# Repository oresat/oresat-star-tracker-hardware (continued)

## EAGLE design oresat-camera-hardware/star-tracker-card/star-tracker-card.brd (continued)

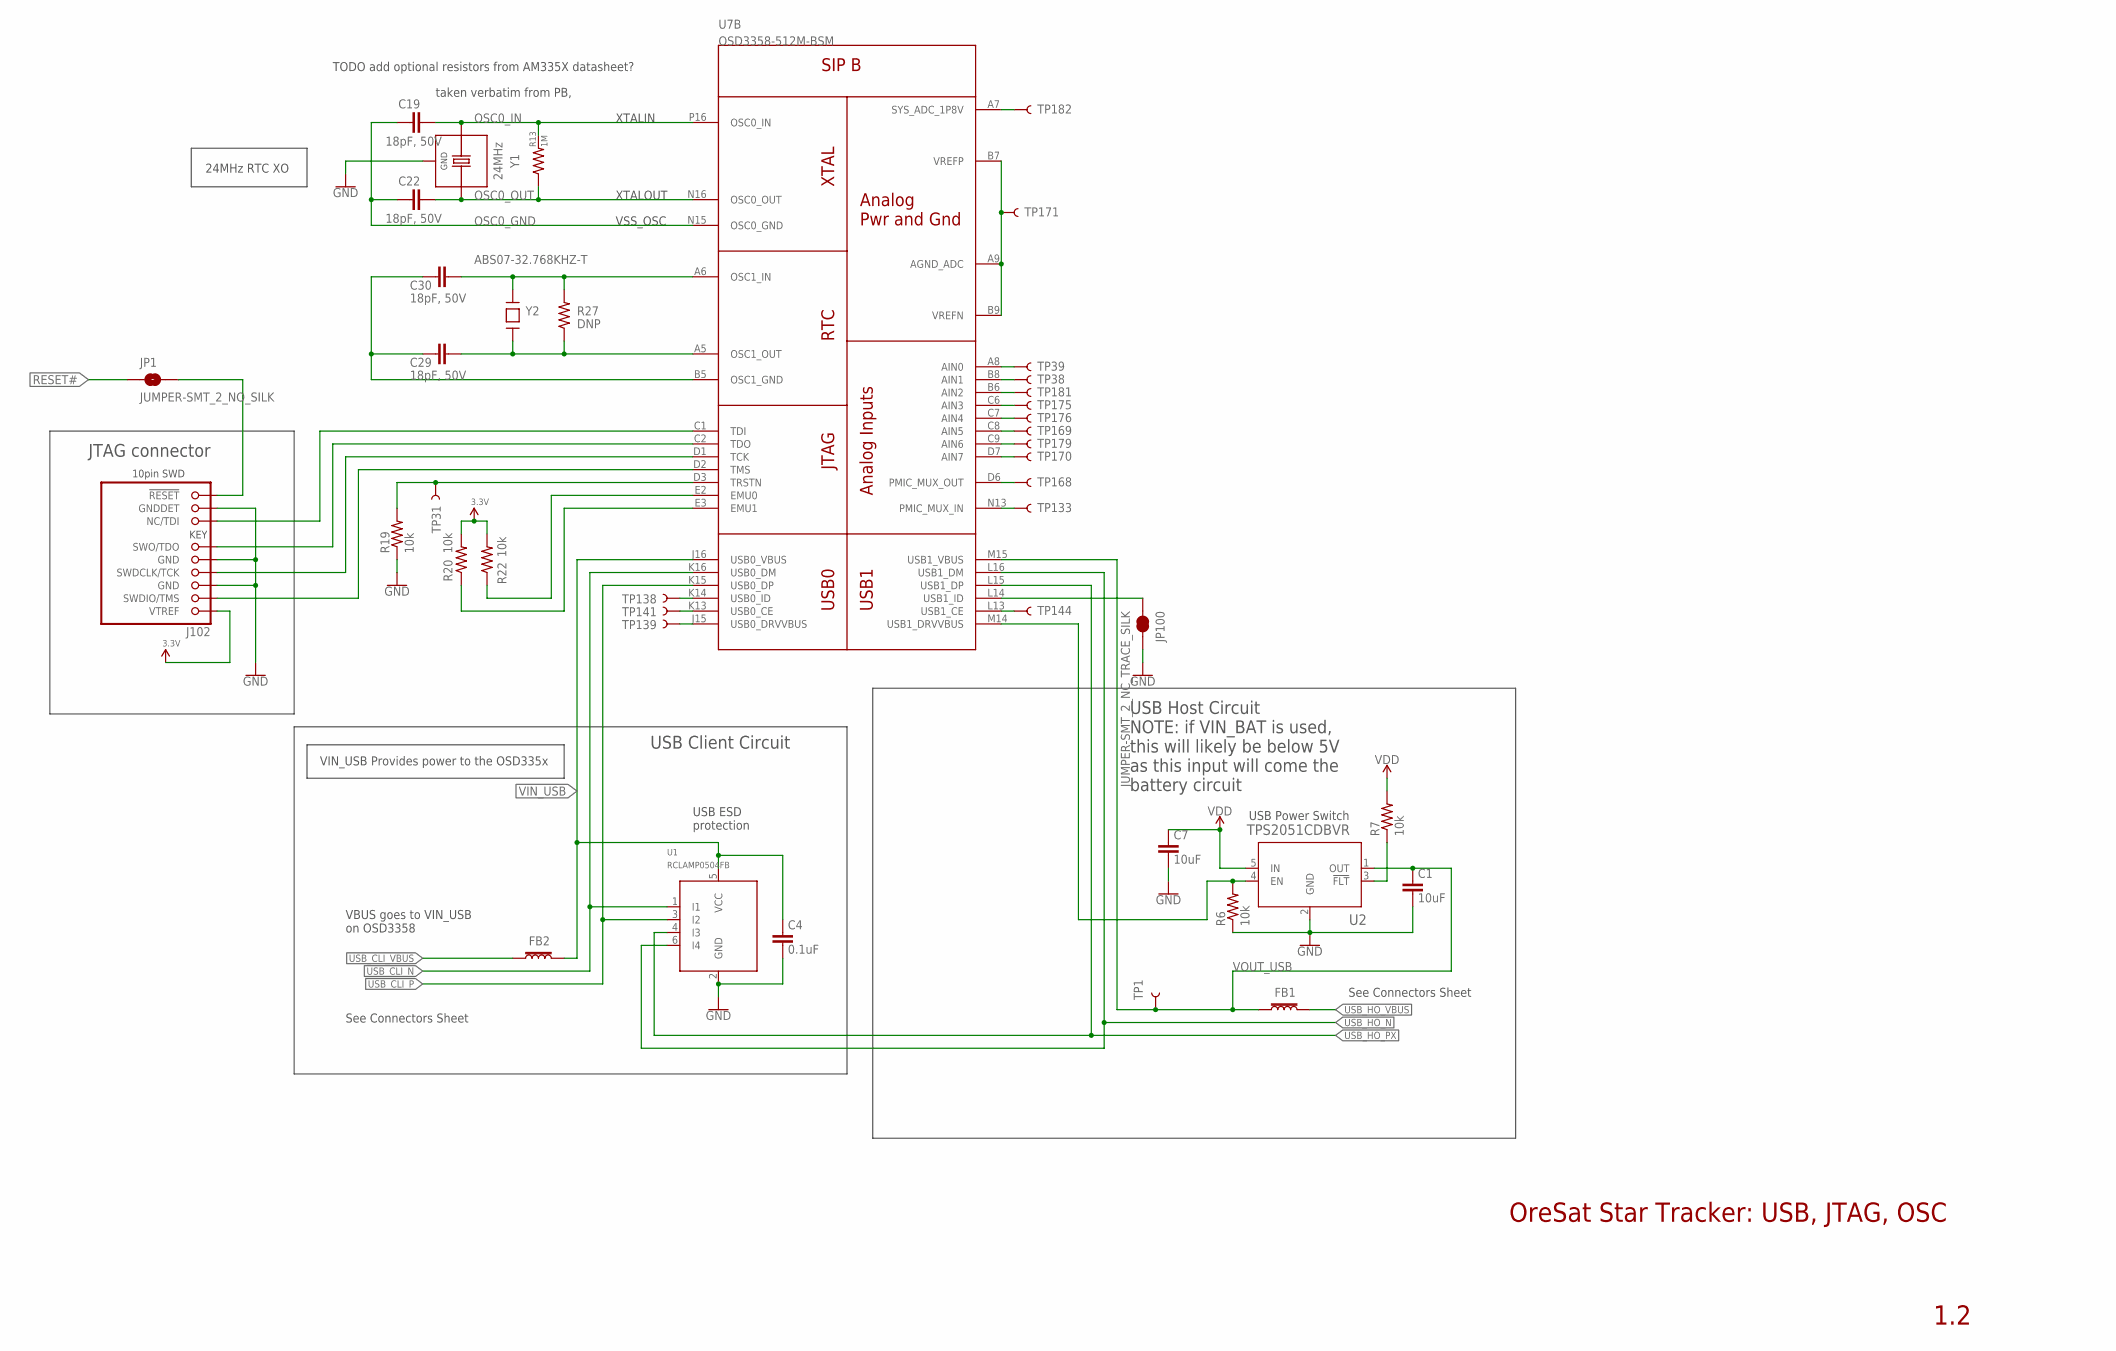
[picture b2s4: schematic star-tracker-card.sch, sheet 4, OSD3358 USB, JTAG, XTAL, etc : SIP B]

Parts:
C1, C7: 10uF; .0805-B
C4: 0.1uF; .0603-A
C19, C22, C29, C30: 18pF, 50V; .0603-A
FB1, FB2: 30Ω/1.8A; 0603; MPN BLM18KG300JH1D
J102: FTSH-105-XX-X-DV-K; CON10_2X5_DUK_FTSH
JP1: JUMPER-SMT_2_NO_SILK; SMT-JUMPER_2_NO_SILK
JP100: JUMPER-SMT_2_NC_TRACE_SILK; SMT-JUMPER_2_NC_TRACE_SILK
R6, R7, R19, R20, R22: 10k; .0603-A
R13: 1M; .0603-A
R27: DNP; .0603-A
TP1, TP31, TP38, TP39, TP133, TP138, TP139, TP141, TP144, TP168, TP169, TP170, TP171, TP175, TP176, TP179, TP181, TP182: TEST-POINT3X4; PAD.03X.04
U1: RCLAMP0504FB; SC70-6
U2: TPS2051CDBVR; DBV5
U7: OSD3358-512M-BSM; OSD335X-BGA-256
Y1: 24MHz; 5X3.2-4SMD
Y2: ABS07-32.768KHZ-T; CRYSTAL_3.2X1.5

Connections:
3.3V: J102.1 (VTREF), R20.2, R22.2; also elsewhere on the board
GND: C1.2, C4.2, C7.2, J102.3 (GND), J102.5 (GND), J102.9 (GNDDET), JP100.2, R6.1, R19.1, U1.2 (GND), U2.2 (GND), Y1.2 (GND), Y1.4 (GND); also elsewhere on the board
unnamed: TP171.P$1, U7.A9 (AGND_ADC), U7.B7 (VREFP), U7.B9 (VREFN)
unnamed: TP170.P$1, U7.D7 (AIN7)
unnamed: TP179.P$1, U7.C9 (AIN6)
unnamed: TP169.P$1, U7.C8 (AIN5)
unnamed: TP176.P$1, U7.C7 (AIN4)
unnamed: TP175.P$1, U7.C6 (AIN3)
unnamed: TP181.P$1, U7.B6 (AIN2)
unnamed: TP38.P$1, U7.B8 (AIN1)
unnamed: TP39.P$1, U7.A8 (AIN0)
unnamed: TP141.P$1, U7.K13 (USB0_CE)
unnamed: TP139.P$1, U7.J15 (USB0_DRVVBUS)
unnamed: TP182.P$1, U7.A7 (SYS_ADC_1P8V)
unnamed: TP168.P$1, U7.D6 (PMIC_MUX_OUT)
unnamed: R20.1, U7.E3 (EMU1)
unnamed: TP144.P$1, U7.L13 (USB1_CE)
unnamed: R22.1, U7.E2 (EMU0)
unnamed: JP100.1, U7.L14 (USB1_ID)
unnamed: TP138.P$1, U7.K14 (USB0_ID)
unnamed: J102.10 (!RESET), JP1.2
unnamed: J102.6 (SWO/TDO), U7.C2 (TDO)
unnamed: J102.4 (SWDCLK/TCK), U7.D1 (TCK)
unnamed: J102.2 (SWDIO/TMS), U7.D2 (TMS)
unnamed: R6.2, U2.4 (EN), U7.M14 (USB1_DRVVBUS)
unnamed: R7.1, U2.3 (!FLT)
unnamed: J102.8 (NC/TDI), U7.C1 (TDI)
unnamed: R19.2, TP31.P$1, U7.D3 (TRSTN)
OSC0_GND: C19.1, C22.1, U7.N15 (OSC0_GND)
OSC0_IN: C19.2, R13.2, U7.P16 (OSC0_IN), Y1.1 (X1)
OSC0_OUT: C22.2, R13.1, U7.N16 (OSC0_OUT), Y1.3 (X2)
OSC1_GND1: C29.2, C30.2, U7.B5 (OSC1_GND)
OSC1_IN1: C30.1, R27.2, U7.A6 (OSC1_IN), Y2.P$2
OSC1_OUT1: C29.1, R27.1, U7.A5 (OSC1_OUT), Y2.P$1
PMIC_MUX_IN: TP133.P$1, U7.N13 (PMIC_MUX_IN)
RESET#: JP1.1; also elsewhere on the board
USB_CLI_N: U1.1 (I1), U7.K16 (USB0_DM); also elsewhere on the board
USB_CLI_P: U1.3 (I2), U7.K15 (USB0_DP); also elsewhere on the board
USB_CLI_VBUS: FB2.1; also elsewhere on the board
USB_HO_N: U1.6 (I4), U7.L16 (USB1_DM); also elsewhere on the board
USB_HO_PX: U1.4 (I3), U7.L15 (USB1_DP); also elsewhere on the board
USB_HO_VBUS: FB1.2; also elsewhere on the board
VDD: C7.1, R7.2, U2.5 (IN); also elsewhere on the board
VIN_USB: C4.1, FB2.2, U1.5 (VCC), U7.J16 (USB0_VBUS); also elsewhere on the board
VOUT_USB: C1.1, FB1.1, TP1.P$1, U2.1 (OUT), U7.M15 (USB1_VBUS)

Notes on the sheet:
taken verbatim from PB,
VBUS goes to VIN_USB on OSD3358
USB ESD protection
USB Host Circuit NOTE: if VIN_BAT is used, this will likely be below 5V as this input will come the battery circuit
USB Power Switch
JTAG connector
USB Client Circuit
24MHz RTC XO
See Connectors Sheet
TODO add optional resistors from AM335X datasheet?
XTALIN
XTALOUT
VSS_OSC
VIN_USB Provides power to the OSD335x
OreSat Star Tracker: USB, JTAG, OSC
1.2

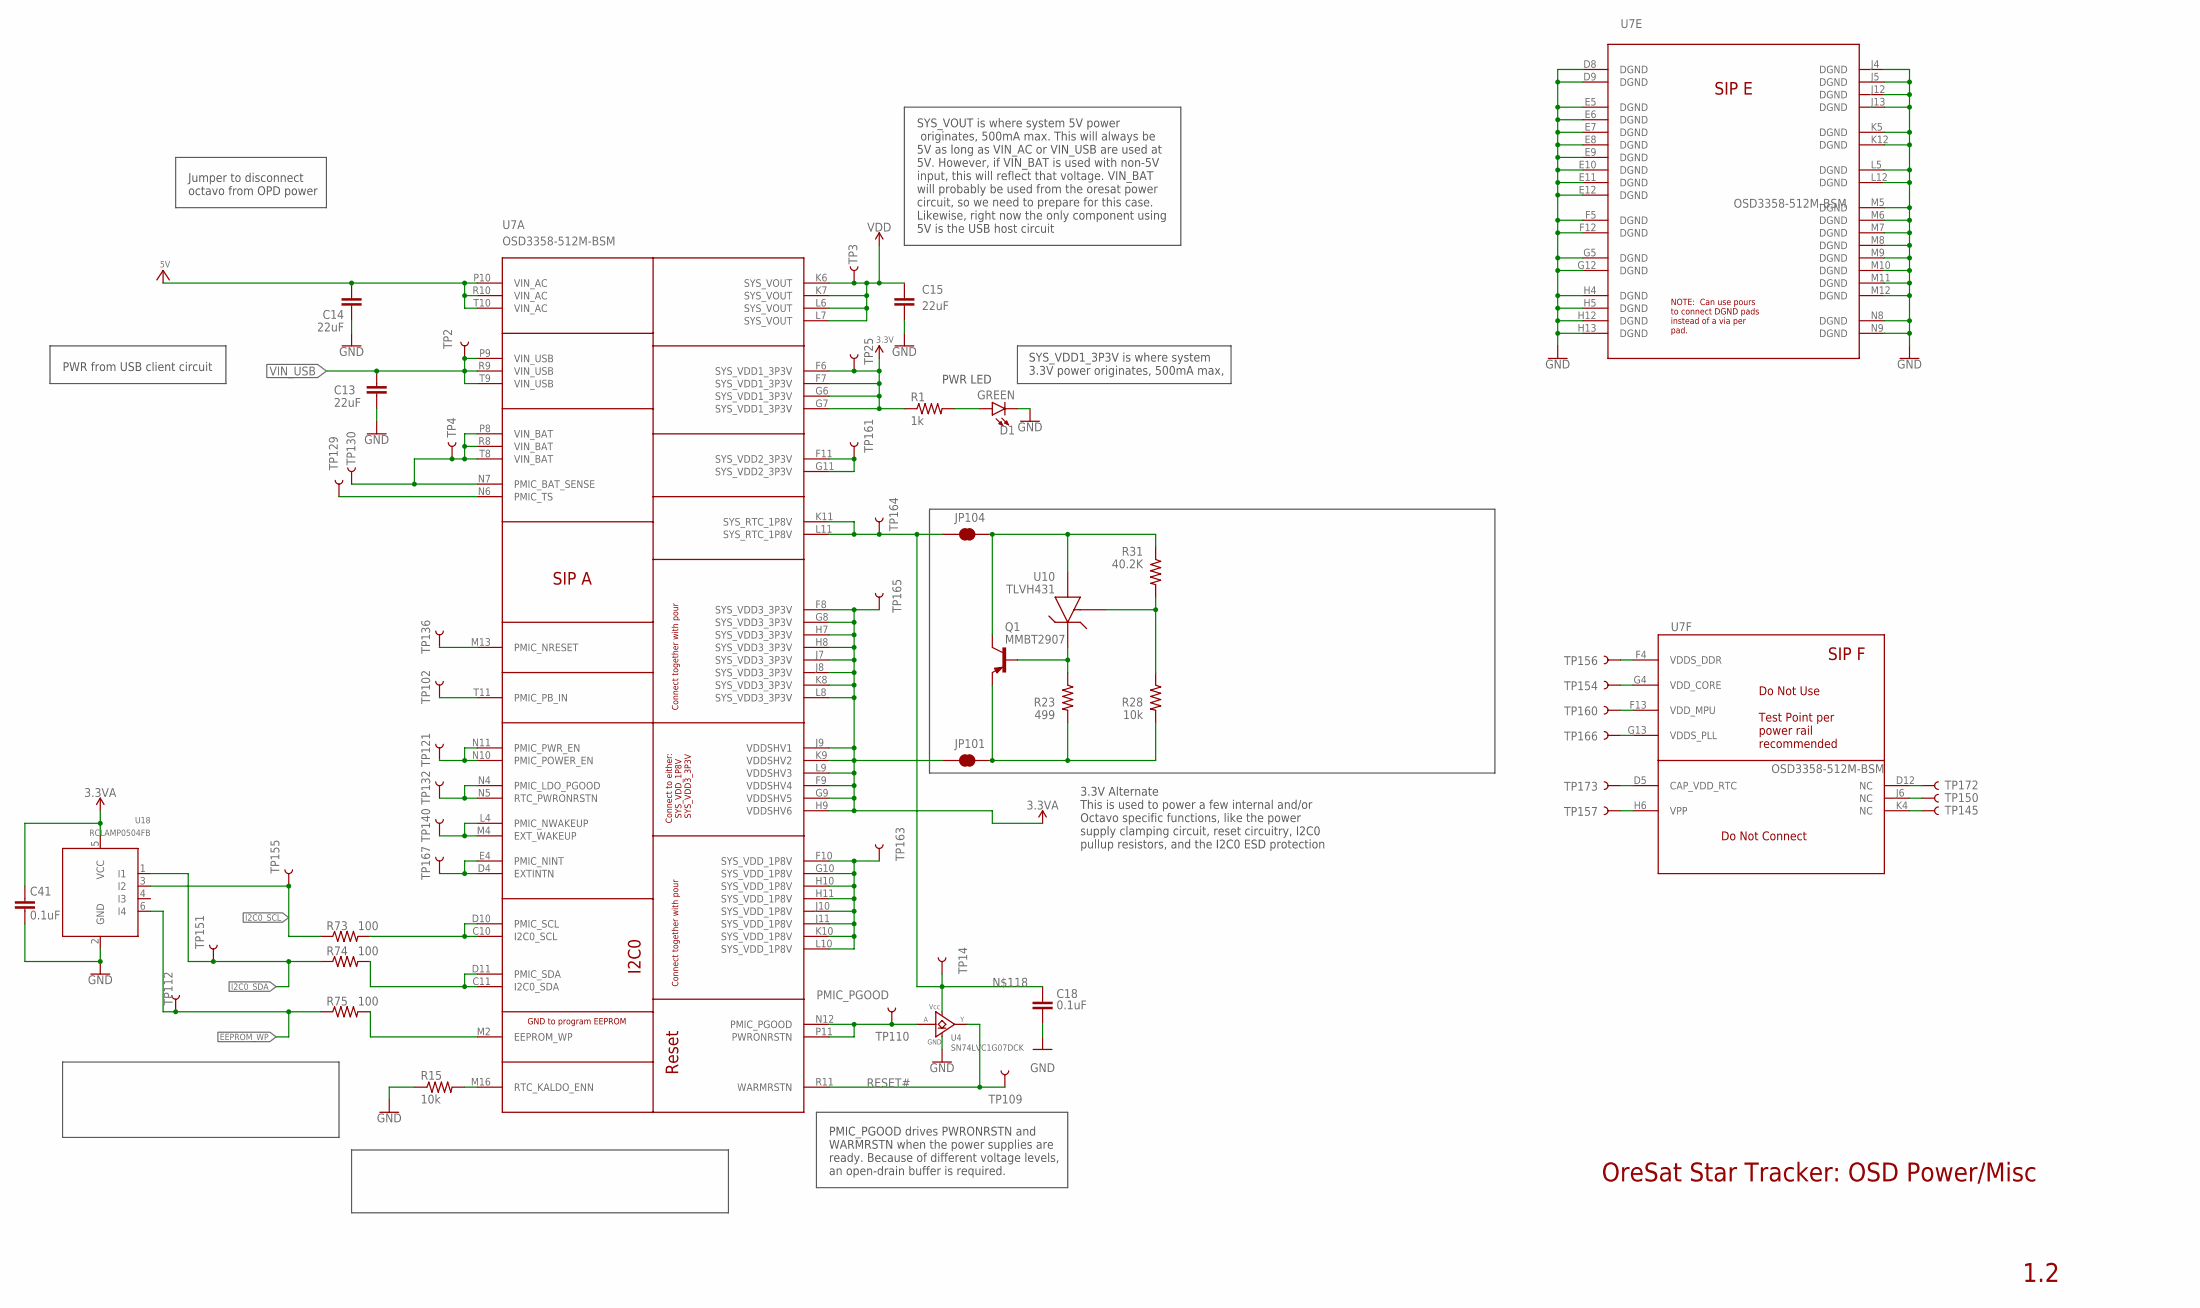
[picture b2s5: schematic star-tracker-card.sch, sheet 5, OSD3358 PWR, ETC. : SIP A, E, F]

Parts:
C13, C14, C15: 22uF; C1210
C18, C41: 0.1uF; .0603-A
D1: GREEN; LED-0603
JP101, JP104: JUMPER-SMT_2_NC_TRACE_SILK; SMT-JUMPER_2_NC_TRACE_SILK
Q1: MMBT2907; SOT23-BEC
R1: 1k; .0603-A
R15, R28: 10k; .0603-A
R23: 499; .0603-A
R31: 40.2K; .0603-A
R73, R74, R75: 100; .0603-A
TP2, TP3, TP4, TP14, TP25, TP102, TP109, TP110, TP112, TP121, TP129, TP130, TP132, TP136, TP140, TP145, TP150, TP151, TP154, TP155, TP156, TP157, TP160, TP161, TP163, TP164, TP165, TP166, TP167, TP172, TP173: TEST-POINT3X4; PAD.03X.04
U4: SN74LVC1G07DCK; C70(TI-DCK)
U7: OSD3358-512M-BSM; OSD335X-BGA-256
U10: TLVH431; SOT23-3
U18: RCLAMP0504FB; SC70-6

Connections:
3.3V: R1.1, TP25.P$1, U7.F6 (SYS_VDD1_3P3V), U7.F7 (SYS_VDD1_3P3V), U7.G6 (SYS_VDD1_3P3V), U7.G7 (SYS_VDD1_3P3V); also elsewhere on the board
3.3VA: C41.1, JP101.1, TP165.P$1, U7.F8 (SYS_VDD3_3P3V), U7.F9 (VDDSHV4), U7.G8 (SYS_VDD3_3P3V), U7.G9 (VDDSHV5), U7.H7 (SYS_VDD3_3P3V), U7.H8 (SYS_VDD3_3P3V), U7.H9 (VDDSHV6), U7.J7 (SYS_VDD3_3P3V), U7.J8 (SYS_VDD3_3P3V), U7.J9 (VDDSHV1), U7.K8 (SYS_VDD3_3P3V), U7.K9 (VDDSHV2), U7.L8 (SYS_VDD3_3P3V), U7.L9 (VDDSHV3), U18.5 (VCC)
5V: C14.1, U7.P10 (VIN_AC), U7.R10 (VIN_AC), U7.T10 (VIN_AC); also elsewhere on the board
EEPROM_WP: R75.1, TP112.P$1, U18.6 (I4); also elsewhere on the board
GND: C13.2, C14.2, C15.2, C18.2, C41.2, D1.C, R15.1, U4.3 (GND), U7.D8 (DGND), U7.D9 (DGND), U7.E5 (DGND), U7.E6 (DGND), U7.E7 (DGND), U7.E8 (DGND), U7.E9 (DGND), U7.E10 (DGND), U7.E11 (DGND), U7.E12 (DGND), U7.F5 (DGND), U7.F12 (DGND), U7.G5 (DGND), U7.G12 (DGND), U7.H4 (DGND), U7.H5 (DGND), U7.H12 (DGND), U7.H13 (DGND), U7.J4 (DGND), U7.J5 (DGND), U7.J12 (DGND), U7.J13 (DGND), U7.K5 (DGND), U7.K12 (DGND), U7.L5 (DGND), U7.L12 (DGND), U7.M5 (DGND), U7.M6 (DGND), U7.M7 (DGND), U7.M8 (DGND), U7.M9 (DGND), U7.M10 (DGND), U7.M11 (DGND), U7.M12 (DGND), U7.N8 (DGND), U7.N9 (DGND), U18.2 (GND); also elsewhere on the board
I2C0_SCL: R73.1, TP155.P$1, U18.3 (I2); also elsewhere on the board
I2C0_SDA: R74.1, TP151.P$1, U18.1 (I1); also elsewhere on the board
unnamed: JP101.2, Q1.E, R23.2, R28.2
unnamed: R28.1, R31.2, U10.1 (REF)
unnamed: Q1.B, R23.1, U10.2 (CATHODE)
unnamed: TP172.P$1, U7.D12 (NC)
unnamed: TP150.P$1, U7.J6 (NC)
unnamed: TP145.P$1, U7.K4 (NC)
unnamed: TP157.P$1, U7.H6 (VPP)
unnamed: TP173.P$1, U7.D5 (CAP_VDD_RTC)
unnamed: TP166.P$1, U7.G13 (VDDS_PLL)
unnamed: TP160.P$1, U7.F13 (VDD_MPU)
unnamed: TP154.P$1, U7.G4 (VDD_CORE)
unnamed: TP156.P$1, U7.F4 (VDDS_DDR)
unnamed: D1.A, R1.2
unnamed: R74.2, U7.C11 (I2C0_SDA), U7.D11 (PMIC_SDA)
unnamed: R75.2, U7.M2 (EEPROM_WP)
unnamed: R73.2, U7.C10 (I2C0_SCL), U7.D10 (PMIC_SCL)
unnamed: C18.1, JP104.1, TP14.P$1, TP164.P$1, U4.5 (VCC), U7.K11 (SYS_RTC_1P8V), U7.L11 (SYS_RTC_1P8V)
unnamed: TP4.P$1, TP130.P$1, U7.N7 (PMIC_BAT_SENSE), U7.P8 (VIN_BAT), U7.R8 (VIN_BAT), U7.T8 (VIN_BAT)
unnamed: TP129.P$1, U7.N6 (PMIC_TS)
unnamed: TP161.P$1, U7.F11 (SYS_VDD2_3P3V), U7.G11 (SYS_VDD2_3P3V)
unnamed: JP104.2, Q1.C, R31.1, U10.3 (ANODE)
unnamed: TP163.P$1, U7.F10 (SYS_VDD_1P8V), U7.G10 (SYS_VDD_1P8V), U7.H10 (SYS_VDD_1P8V), U7.H11 (SYS_VDD_1P8V), U7.J10 (SYS_VDD_1P8V), U7.J11 (SYS_VDD_1P8V), U7.K10 (SYS_VDD_1P8V), U7.L10 (SYS_VDD_1P8V)
unnamed: TP167.P$1, U7.D4 (EXTINTN), U7.E4 (PMIC_NINT)
unnamed: TP140.P$1, U7.L4 (PMIC_NWAKEUP), U7.M4 (EXT_WAKEUP)
unnamed: TP132.P$1, U7.N4 (PMIC_LDO_PGOOD), U7.N5 (RTC_PWRONRSTN)
unnamed: TP121.P$1, U7.N10 (PMIC_POWER_EN), U7.N11 (PMIC_PWR_EN)
unnamed: TP102.P$1, U7.T11 (PMIC_PB_IN)
unnamed: TP136.P$1, U7.M13 (PMIC_NRESET)
unnamed: R15.2, U7.M16 (RTC_KALDO_ENN)
PMIC_PGOOD: TP110.P$1, U4.2 (A), U7.N12 (PMIC_PGOOD), U7.P11 (PWRONRSTN)
RESET#: TP109.P$1, U4.4 (Y), U7.R11 (WARMRSTN); also elsewhere on the board
VDD: C15.1, TP3.P$1, U7.K6 (SYS_VOUT), U7.K7 (SYS_VOUT), U7.L6 (SYS_VOUT), U7.L7 (SYS_VOUT); also elsewhere on the board
VIN_USB: C13.1, TP2.P$1, U7.P9 (VIN_USB), U7.R9 (VIN_USB), U7.T9 (VIN_USB); also elsewhere on the board

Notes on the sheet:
SYS_VOUT is where system 5V power originates, 500mA max. This will always be 5V as long as VIN_AC or VIN_USB are used at 5V. However, if VIN_BAT is used with non-5V input, this will reflect that voltage. VIN_BAT will probably be used from the oresat power circuit, so we need to prepare for this cas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
SYS_VDD1_3P3V is where system 3.3V power originates, 500mA max,
PWR LED
PMIC_PGOOD drives PWRONRSTN and WARMRSTN when the power supplies are ready. Because of different voltage levels, an open-drain buffer is required.
PWR from USB client circuit
Jumper to disconnect octavo from OPD power
3.3V Alternate This is used to power a few internal and/or Octavo specific functions, like the power supply clamping circuit, reset circuitry, I2C0 pullup resistors, and the I2C0 ESD protection
OreSat Star Tracker: OSD Power/Misc
1.2

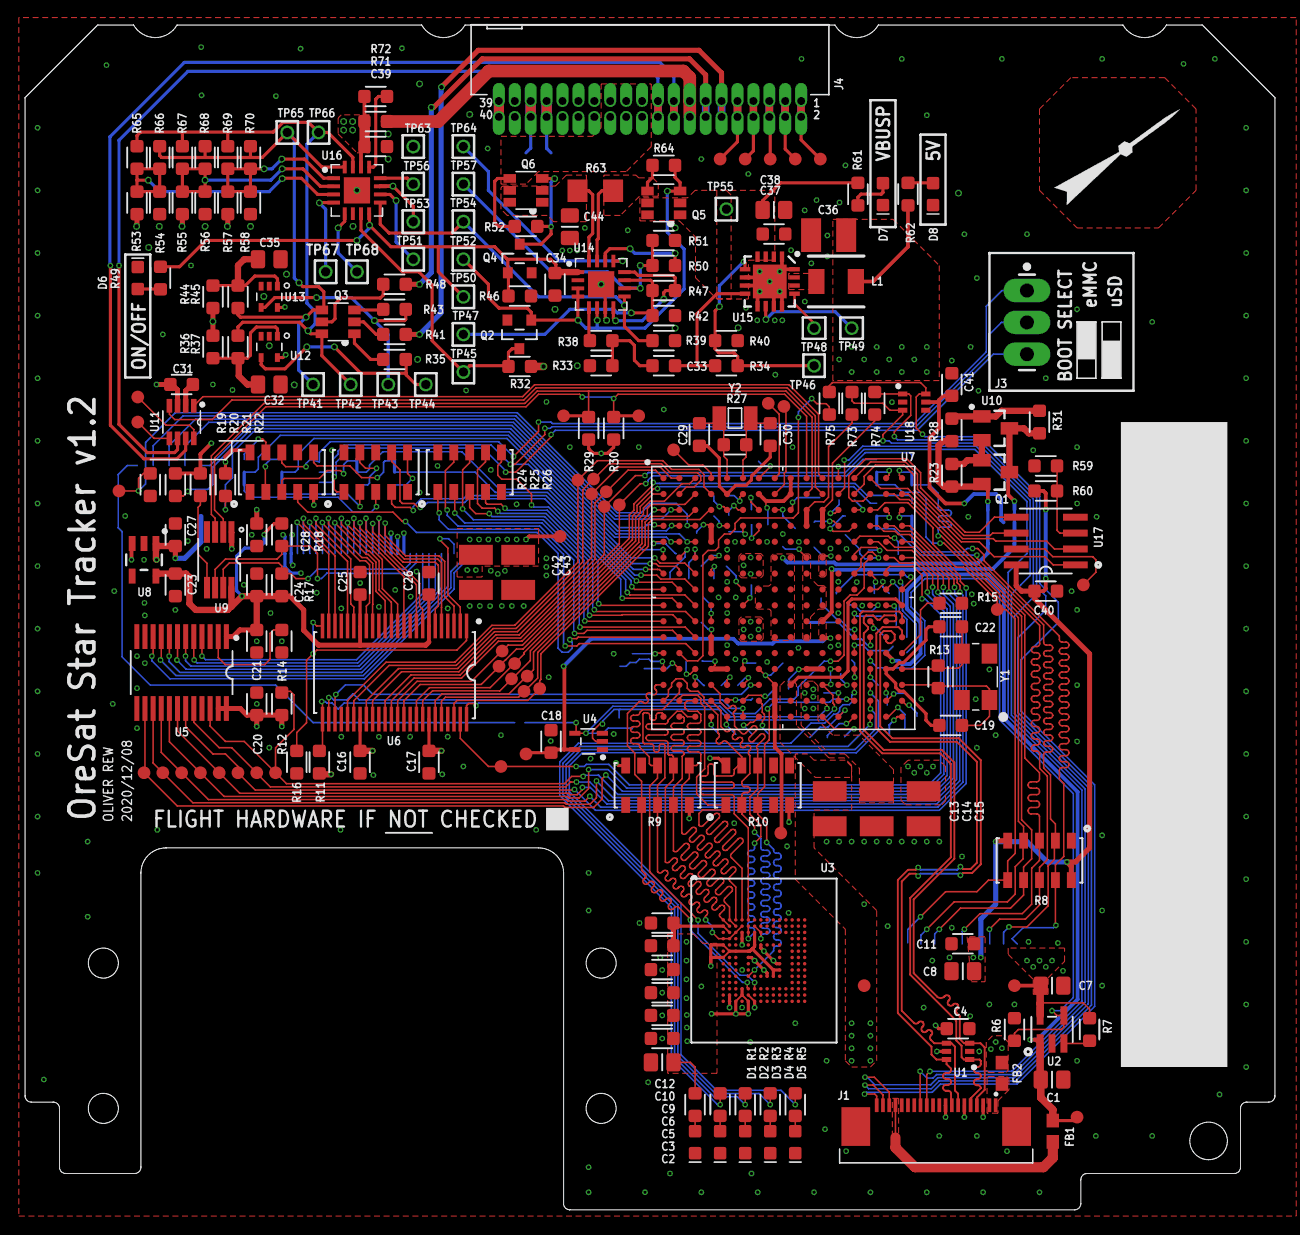
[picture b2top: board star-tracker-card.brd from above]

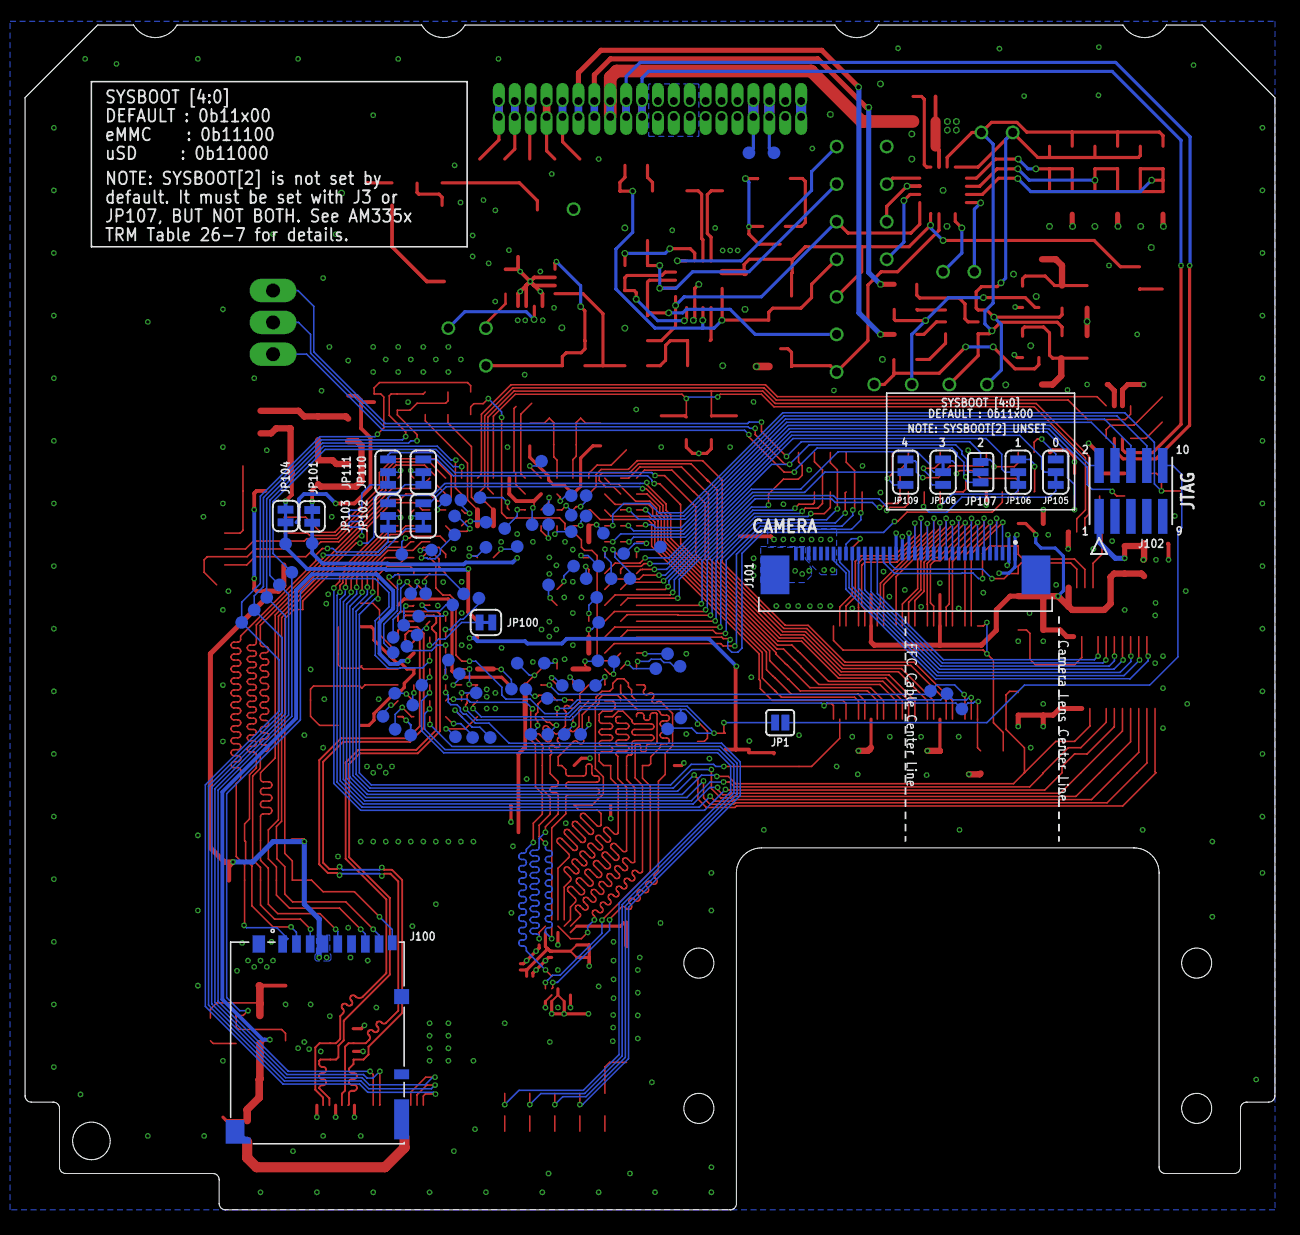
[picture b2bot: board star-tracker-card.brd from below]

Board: 4 copper layers, 99.8 x 94.6 mm, 330 parts (101 on the bottom side), 299 nets.

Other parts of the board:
U$2: CAMERA_BOARD_TOP_DIMS
U$3: PSAS_LOGO_10X10

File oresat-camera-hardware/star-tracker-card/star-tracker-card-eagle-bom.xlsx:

| Qty | Value | Device | Package | Parts | Description | DPN | MPN
N | 1 | TFM-120-01-L-D-RA | J-SAMTEC-TFM-120-X1-XXX-D-RA | J-SAMTEC-TFM-120-X1-XXX-D-RA | J4 |  | SAM10145-ND | TFM-120-01-L-D-RA
N | 1 | OSD3358-512M-BSM | OSD3358-512M-BSM | OSD335X-BGA-256 | U7 | Octavo Systems LLC OSD335x Family SiP: 21mm x 21mm, 1.27mm pitch 256 pin BGA co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 | 1676-1002-ND | OSD3358-512M-BSM
x | 6 | 10uF | C-EU0805-B | .0805-B | C1, C2, C7, C8, C38, C44 | CAPACITOR, European symbol
x | 6 | 22uF | C-EUC1210 | C1210 | C13, C14, C15, C36, C42, C43 | CAPACITOR, European symbol
x | 4 | 18pF, 50V | C-EU0603-A | .0603-A | C19, C22, C29, C30 | CAPACITOR, European symbol
x | 10 | 1uF | C-EU0603-A | .0603-A | C3, C5, C6, C9, C10, C12, C23, C27, C33, C34, C37 | CAPACITOR, European symbol
x | 2 | 1uF | C-EU0805-B-NOSILK | .0805-B-NOSILK | C32, C35 | CAPACITOR, European symbol
x | 15 | 0.1uF | C-EU0603-A | .0603-A | C4, C11, C16, C17, C18, C20, C21, C24, C25, C26, C28, C31, C39, C40, C41 | CAPACITOR, European symbol
x | 3 | GREEN | LED-GREEN0603 | LED-0603 | D1, D7, D8 | Green SMD LED
x | 4 | BLUE | LED-BLUE0603 | LED-0603 | D2, D3, D4, D5 | Blue SMD LED
x | 1 | AMBER | LED-GREEN0603 | LED-0603 | D6 | Green SMD LED
x | 2 | 30Ω/1.8A | FERRITE_BEAD-0603 | 603 | FB1, FB2 | Ferrite Bead (blocks, cores, rings, chokes, etc.) | 490-14027-1-ND | BLM18KG300JH1D
x | 1 | ORESAT-DEBUG-CONNECTOR-CARD | ORESAT-DEBUG-CONNECTOR-CARD | TE_2-1734592-0 | J1 |  | A100287CT-ND | 2-1734592-0
x | 1 | 3-1734592-64-1734592-0 | 3-1734592-64-1734592-0 | TE_3-1734592-6 | J101 |  | A100291CT-ND | 3-1734592-6
x | 1 | 6.8u | L-ECS-MPI4040 | ECS-MPI4040 | L1 |  | XC2337CT-ND | ECS-MPI4040R4-6R8-R
x | 1 | MMBT2907 | MMBT2907SMD | SOT23-BEC | Q1 | PNP Transistror | MMBT2907A-FDICT-ND | MMBT2907A-7-F
x | 2 | PMV45EN | PMV45EN | SOT23 | Q2, Q4 |  | 1727-2307-1-ND | PMV45EN2R
x | 1 | DMP2240UDM | MOSFET-PCH-SOT23-6 | SOT23-6 | Q3 | Dual P channel MOSFETs in an SOT23-6 | DMP2240UDMDICT-ND | DMP2240UDM-7
x | 2 | MOSFET-PCH-SOT23-6 | MOSFET-PCH-SOT23-6 | SOT23-6 | Q5, Q6 | P channel MOSFET in an SOT23-6 | DMP3050LVT-7DICT-ND | DMP3050LVT-7
x | 5 | 1k | R-US_0603-A | .0603-A | R1, R2, R3, R4, R5 | RESISTOR, American symbol
x | 3 | 1M | R-US_0603-A | .0603-A | R13, R36, R44 | RESISTOR, American symbol
x | 4 | 4.7k | R-US_0603-A | .0603-A | R17, R18, R29, R30 | RESISTOR, American symbol
x | 1 | 499 | R-US_0603-A | .0603-A | R23 | RESISTOR, American symbol
x | 3 | 100K | EXB-A10P391JC_ARRAY_EXBA-M | ARRAY_EXBA-M | R24, R25, R26 |  | U7104CT-ND | EXB-A10P104J
x | 1 | 40.2K | R-US_0603-A | .0603-A | R31 | RESISTOR, American symbol
x | 2 | 330k | R-US_0603-A | .0603-A | R37, R45 | RESISTOR, American symbol
x | 6 | 100 | R-US_0603-A | .0603-A | R41, R48, R71, R73, R74, R75 | RESISTOR, American symbol
x | 2 | 0 | R-US_0603-A | .0603-A | R47, R50 | RESISTOR, American symbol
x | 3 | 2.7k | R-US_0603-A | .0603-A | R49, R61, R62 | RESISTOR, American symbol
x | 21 | 10k | R-US_0603-A | .0603-A | R6, R7, R11, R12, R14, R15, R16, R19, R20, R21, R22, R28, R32, R34, R35, R39, R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 | RESISTOR, American symbol
x | 1 | 100m | R-US_R1206 | R1206 | R63 | RESISTOR, American symbol
x | 3 | 10K | EXB-A10P391JC_ARRAY_EXBA-M | ARRAY_EXBA-M | R8, R9, R10 |  | U7103CT-ND | EXB-A10P103J
x | 2 | RCLAMP0504FB | RCLAMP0504FB | SC70-6 | U1, U18 |  | RCLAMP0504FBTCTCT-ND | RCLAMP0504FBTCT
x | 1 | TLVH431 | TLVH431 | SOT23-3 | U10 |  | 296-36778-1-ND | TLVH431BQDBZRQ1
x | 1 | TCAN330 | TCAN330 | SOT23-8_TI-DCN | U11 |  | 296-44211-1-ND | TCAN330GDCNT
x | 2 | MIC842LYC5 | MIC842LYC5 | SC70-5 | U12, U13 |  | 576-2927-1-ND | MIC842LYC5
x | 1 | MAX4211FETE | MAX4211 | QFN65P400X400X80-17T210 | U14 |  | MAX4211FETE+-ND | MAX4211FETE+
x | 1 | TPS62112 | TPS6211X | S-PVQFN-16 | U15 | TPS6211x 17-V, 1.5-A, Synchronous Step-Down Converter | 296-39444-1-ND | TPS62112RSAR
x | 1 | MAX7310ATE | MAX7310 | QFN65P400X400X80-17T210 | U16 |  | MAX7310ATE+-ND | MAX7310ATE
x | 1 | TPS2051CDBVR | TPS2051CDBVR | DBV5 | U2 |  | 296-29537-1-ND | TPS2051CDBVR
x | 1 |  | EMMC+RESET+5.1-COMPATIBLE-BA | BGA-153(11.5X13)(EMMC-BA) | U3 | eMMC (embedded multi-media card) memory with optional Reset function | THGBMJG7C2LBAU8-ND | THGBMJG7C2LBAU8
x | 1 | SN74LVC1G07DCK | SN74LVC1G07DCK | C70(TI-DCK) | U4 |  | 296-8486-1-ND | SN74LVC1G07DCKR
x | 1 | SN74LVC8T245MPWREPPW24-M | SN74LVC8T245MPWREPPW24-M | PW24-M | U5 |  | 296-24003-1-ND | ‎SN74LVC8T245MPWREP‎
x | 1 | CLVCH16T245MDGGREP | CLVCH16T245MDGGREP | DGG48-M | U6 |  | 296-23948-1-ND | CLVCH16T245MDGGREP
x | 1 | TLV70028QDDCRQ1 | TLV70028QDDCRQ1 | SOT23-5 | U8 |  | 296-40607-1-ND | TLV70028QDDCRQ1
x | 1 | TCA9509DGKRDGK8-M | TCA9509DGKRDGK8-M | DGK8-M | U9 |  | 296-30283-1-ND | TCA9509DGKR
x | 1 | ABS07-32.768KHZ-T | ABS07-32.768KHZ-T | CRYSTAL_3.2X1.5 | Y2 | 32kHz crystal | 535-9542-1-ND | ABS07-32.768KHZ-T
 | 1 | DM3BT-DSF-PEJS | DM3BT-DSF-PEJS | DM3BT-DSF-PEJS | J100 | HIROSE - microSD Card socket - Reverse on-Board - Push / Push | DM3BT-DSF-PEJS | DM3BT-DSF-PEJS
 | 2 | 665k | R-US_0603-A | .0603-A | R35, R43
 | 1 | 100k | R-US_0603-A | .0603-A | R33
 | 1 | 24MHz | ECS-240-12-30BQ-AEN-TR | 5X3.2-4SMD | Y1 |  | XC2580CT-ND | ECS-240-12-30BQ-AEN-TR

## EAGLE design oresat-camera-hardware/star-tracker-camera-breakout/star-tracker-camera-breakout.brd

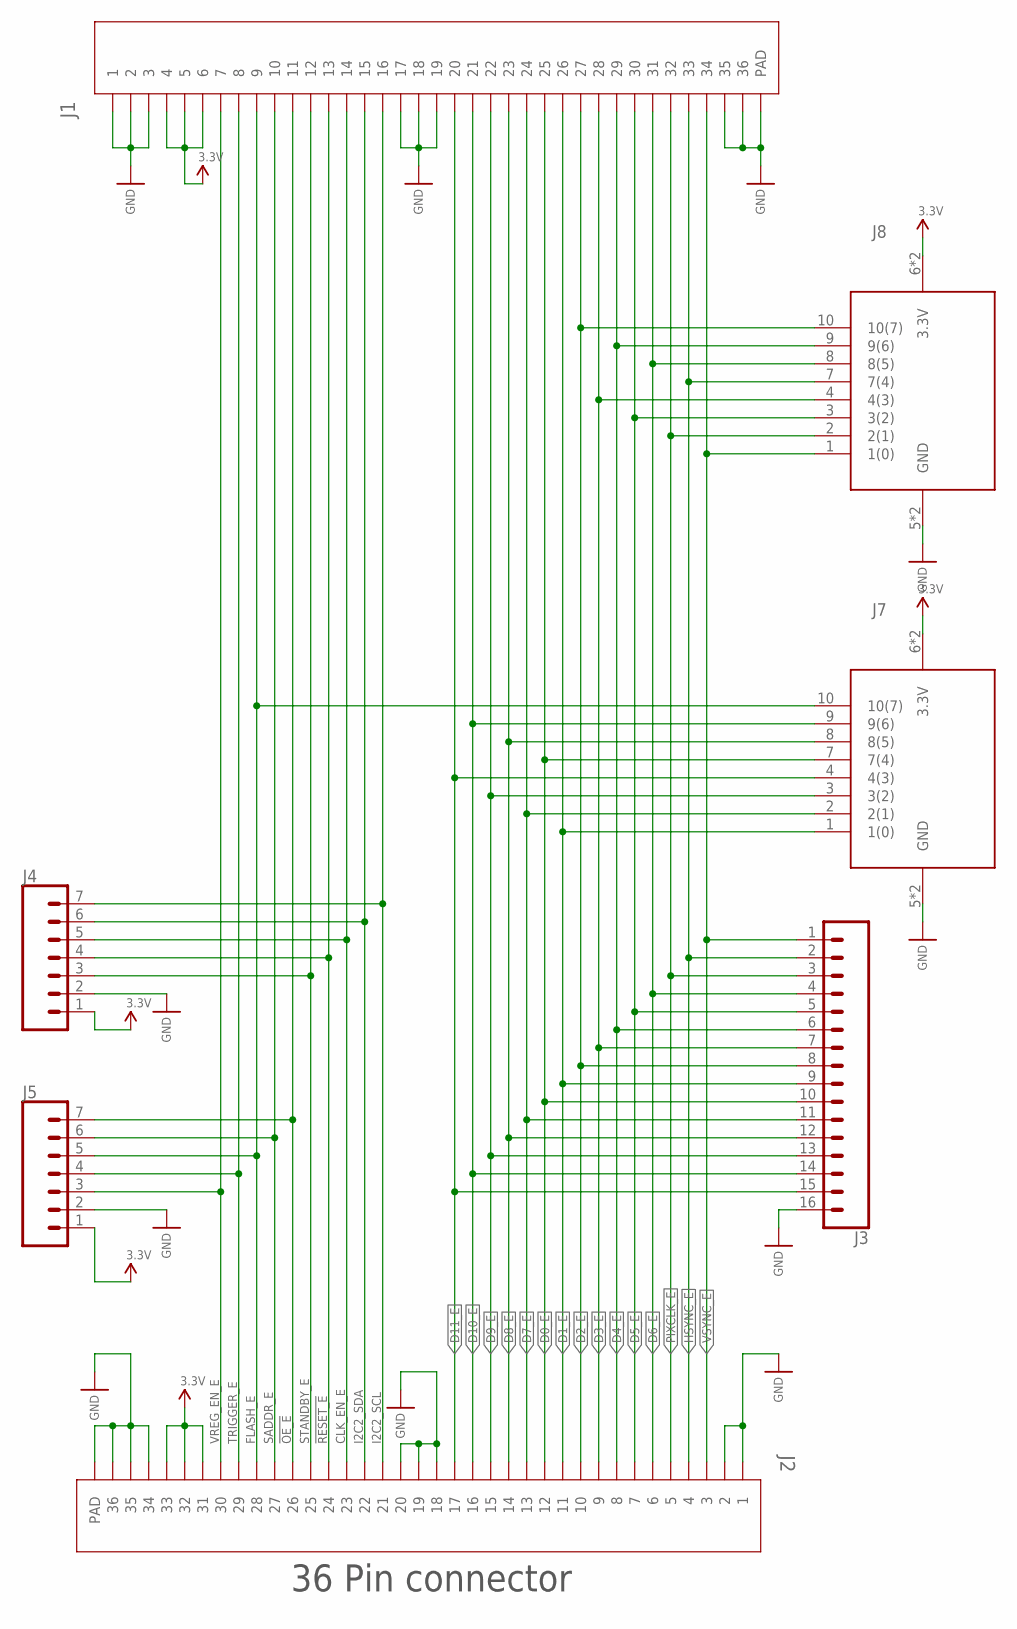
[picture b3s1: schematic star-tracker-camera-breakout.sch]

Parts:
J1, J2: 3-1734592-64-1734592-0; TE_3-1734592-6
J3: CONN_16; 1X16
J4, J5: CONN_07; 1X07
J7, J8: 2X6 FEMALE; PMOD_PERIPH

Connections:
3.3V: J1.4, J1.5, J1.6, J2.31, J2.32, J2.33, J4.1, J5.1, J7.6 (3.3V), J7.12 (3.3V), J8.6 (3.3V), J8.12 (3.3V)
!OE_E: J1.11, J2.26, J5.7
!RESET_E: J1.13, J2.24, J4.4
CLK_EN_E: J1.14, J2.23, J4.5
D0_E: J1.25, J2.12, J3.10, J7.7 (7(4))
D1_E: J1.26, J2.11, J3.9, J7.1 (1(0))
D2_E: J1.27, J2.10, J3.8, J8.10 (10(7))
D3_E: J1.28, J2.9, J3.7, J8.4 (4(3))
D4_E: J1.29, J2.8, J3.6, J8.9 (9(6))
D5_E: J1.30, J2.7, J3.5, J8.3 (3(2))
D6_E: J1.31, J2.6, J3.4, J8.8 (8(5))
D7_E: J1.24, J2.13, J3.11, J7.2 (2(1))
D8_E: J1.23, J2.14, J3.12, J7.8 (8(5))
D9_E: J1.22, J2.15, J3.13, J7.3 (3(2))
D10_E: J1.21, J2.16, J3.14, J7.9 (9(6))
D11_E: J1.20, J2.17, J3.15, J7.4 (4(3))
FLASH_E: J1.9, J2.28, J5.5, J7.10 (10(7))
GND: J1.1, J1.2, J1.3, J1.17, J1.18, J1.19, J1.35, J1.36, J1.S1 (PAD), J1.S2 (PAD), J2.1, J2.2, J2.18, J2.19, J2.20, J2.34, J2.35, J2.36, J2.S1 (PAD), J2.S2 (PAD), J3.16, J4.2, J5.2, J7.5 (GND), J7.11 (GND), J8.5 (GND), J8.11 (GND)
HSYNC_E: J1.33, J2.4, J3.2, J8.7 (7(4))
I2C2_SCL: J1.16, J2.21, J4.7
I2C2_SDA: J1.15, J2.22, J4.6
PIXCLK_E: J1.32, J2.5, J3.3, J8.2 (2(1))
SADDR_E: J1.10, J2.27, J5.6
STANDBY_E: J1.12, J2.25, J4.3
TRIGGER_E: J1.8, J2.29, J5.4
VREG_EN_E: J1.7, J2.30, J5.3
VSYNC_E: J1.34, J2.3, J3.1, J8.1 (1(0))

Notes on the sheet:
36 Pin connector

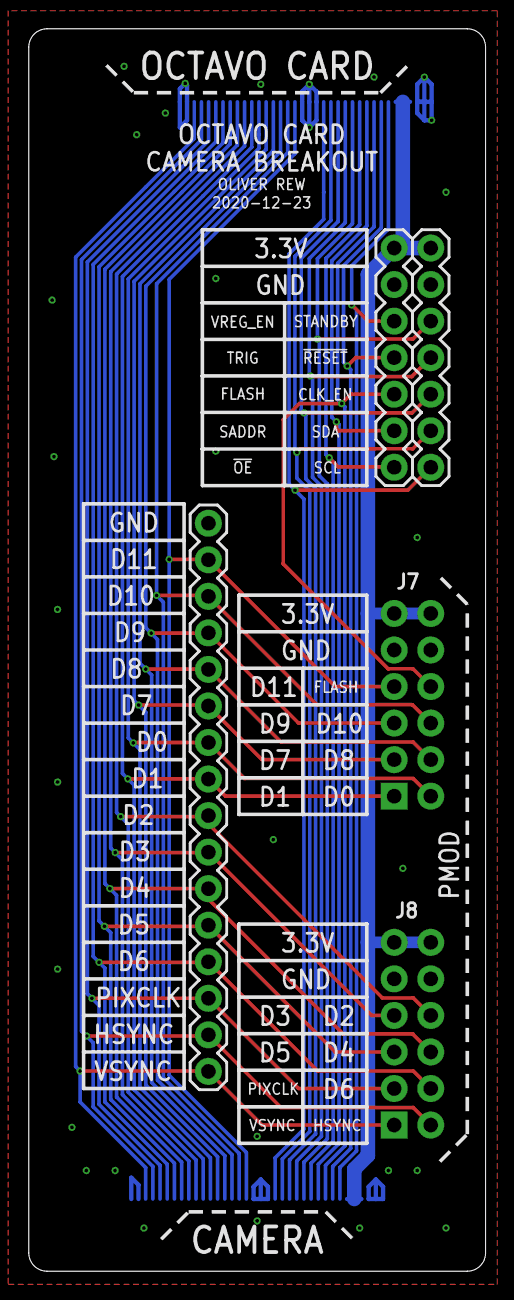
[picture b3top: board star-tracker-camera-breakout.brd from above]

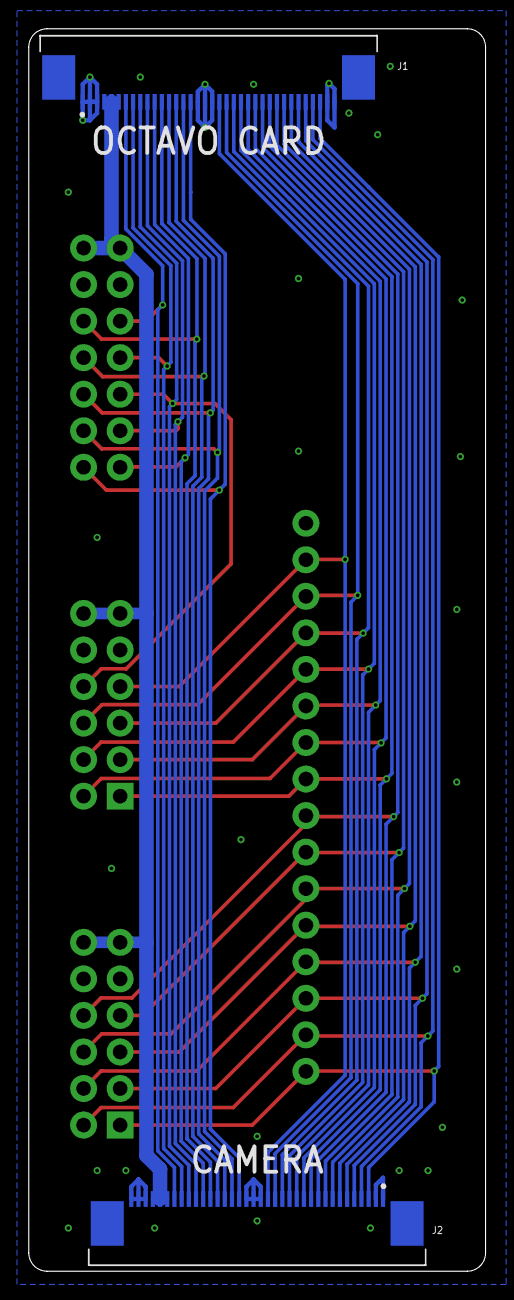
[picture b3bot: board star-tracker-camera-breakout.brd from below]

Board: 2 copper layers, 31.8 x 86.4 mm, 7 parts (2 on the bottom side), 27 nets.

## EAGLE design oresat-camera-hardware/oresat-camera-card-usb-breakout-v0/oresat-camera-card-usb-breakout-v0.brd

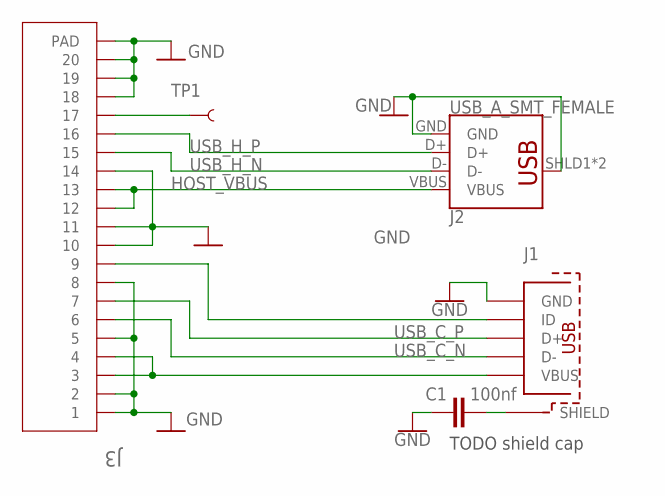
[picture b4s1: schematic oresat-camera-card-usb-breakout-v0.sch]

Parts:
C1: 100nf; .0603-A
J1: MICRO-USB-SOCKET; 629105136821
J2: USB_A_SMT_FEMALE; USB-A-S-SILK-FEMALE
J3: 2-1734592-0; TE_2-1734592-0
TP1: TEST-POINTPOGO_PTH; 1X01_NO_SILK

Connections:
CLIENT_VBUS: J1.1 (VBUS), J3.3, J3.4
GND: C1.1, J1.5 (GND), J2.GND, J2.SHLD1 (SHIELD), J2.SHLD2 (SHIELD), J3.1, J3.2, J3.5, J3.8, J3.10, J3.11, J3.14, J3.18, J3.19, J3.20, J3.S1 (PAD), J3.S2 (PAD)
HOST_VBUS: J2.VBUS, J3.12, J3.13
unnamed: C1.2, J1.SHELL (SHIELD), J1.SHELL1 (SHIELD), J1.SHELL2 (SHIELD), J1.SHELL3 (SHIELD)
unnamed: J3.17, TP1.1
unnamed: J1.4 (ID), J3.9
USB_C_N: J1.2 (D-), J3.6
USB_C_P: J1.3 (D+), J3.7
USB_H_N: J2.D-, J3.15
USB_H_P: J2.D+, J3.16

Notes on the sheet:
TODO shield cap

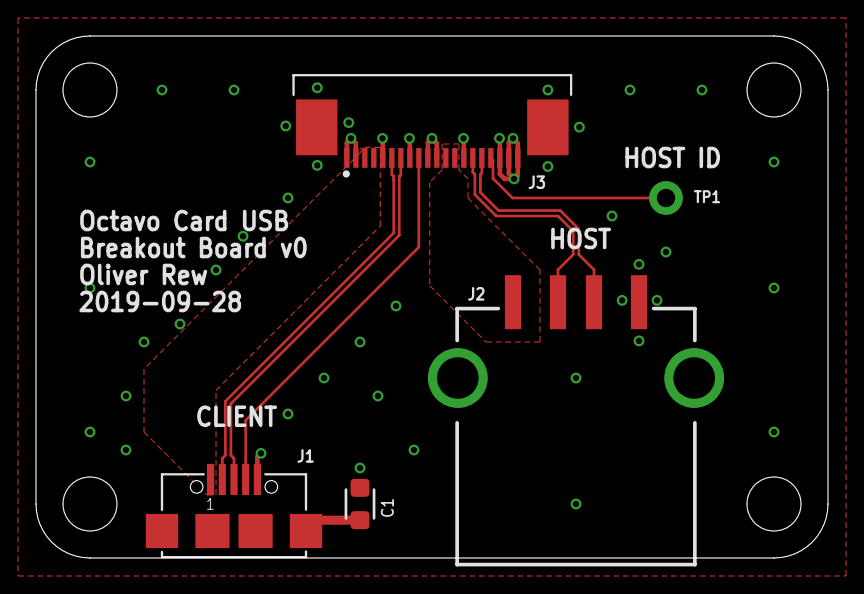
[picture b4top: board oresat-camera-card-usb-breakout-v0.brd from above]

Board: 2 copper layers, 44.0 x 29.0 mm, 5 parts (0 on the bottom side), 10 nets.
